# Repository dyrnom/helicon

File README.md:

# helicon
A split, hall effect/regular mx compatible keyboard with a custom layout

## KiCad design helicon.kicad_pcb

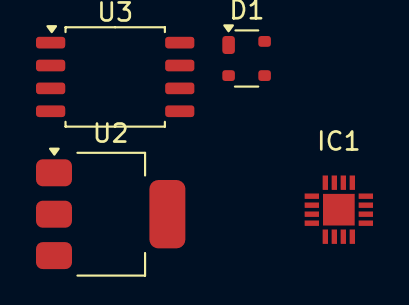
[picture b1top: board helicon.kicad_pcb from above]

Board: 2 copper layers, 4 parts (0 on the bottom side), 3 nets, no tracks yet.

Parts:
D1: PRTR5V0U2X; SOT-143
IC1: TLA2528IRTER; QFN50P300X300X80-17N
U2: NCP1117-3.3_SOT223; SOT-223-3_TabPin2
U3: W25Q128JVS; SOIC-8_5.3x5.3mm_P1.27mm

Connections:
L.3V3: U2.2 (VO), U3.8 (VCC)
L.5V: D1.4 (VCC), U2.3 (VI)
L.GND: D1.1 (GND), U2.1 (GND), U3.4 (GND)

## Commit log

2026-03-21 mcu schematic finished
